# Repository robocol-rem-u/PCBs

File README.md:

# PCBs

PCBs Eagle designs that power REM-U

## Getting Started

1. Install Eagle (students)
2. Open board and schematics

## Built With

* [Eagle](https://www.autodesk.com/products/eagle/overview) - Autodesk EAGLE is powerful, easy-to-use PCB design and schematic software

## Authors

* **Miguel Angel Díaz** - *PCB Design*
* **Oscar Díaz Caballero** - *GitHub Upload* - [alegis277](https://github.com/alegis277)

See also the list of [contributors](https://github.com/robocol-rem-u/PCBs/graphs/contributors) who participated in this project.

## License

This project is licensed under the GNU General Public License v3.0 - see the [LICENSE.txt](LICENSE.txt) file for details

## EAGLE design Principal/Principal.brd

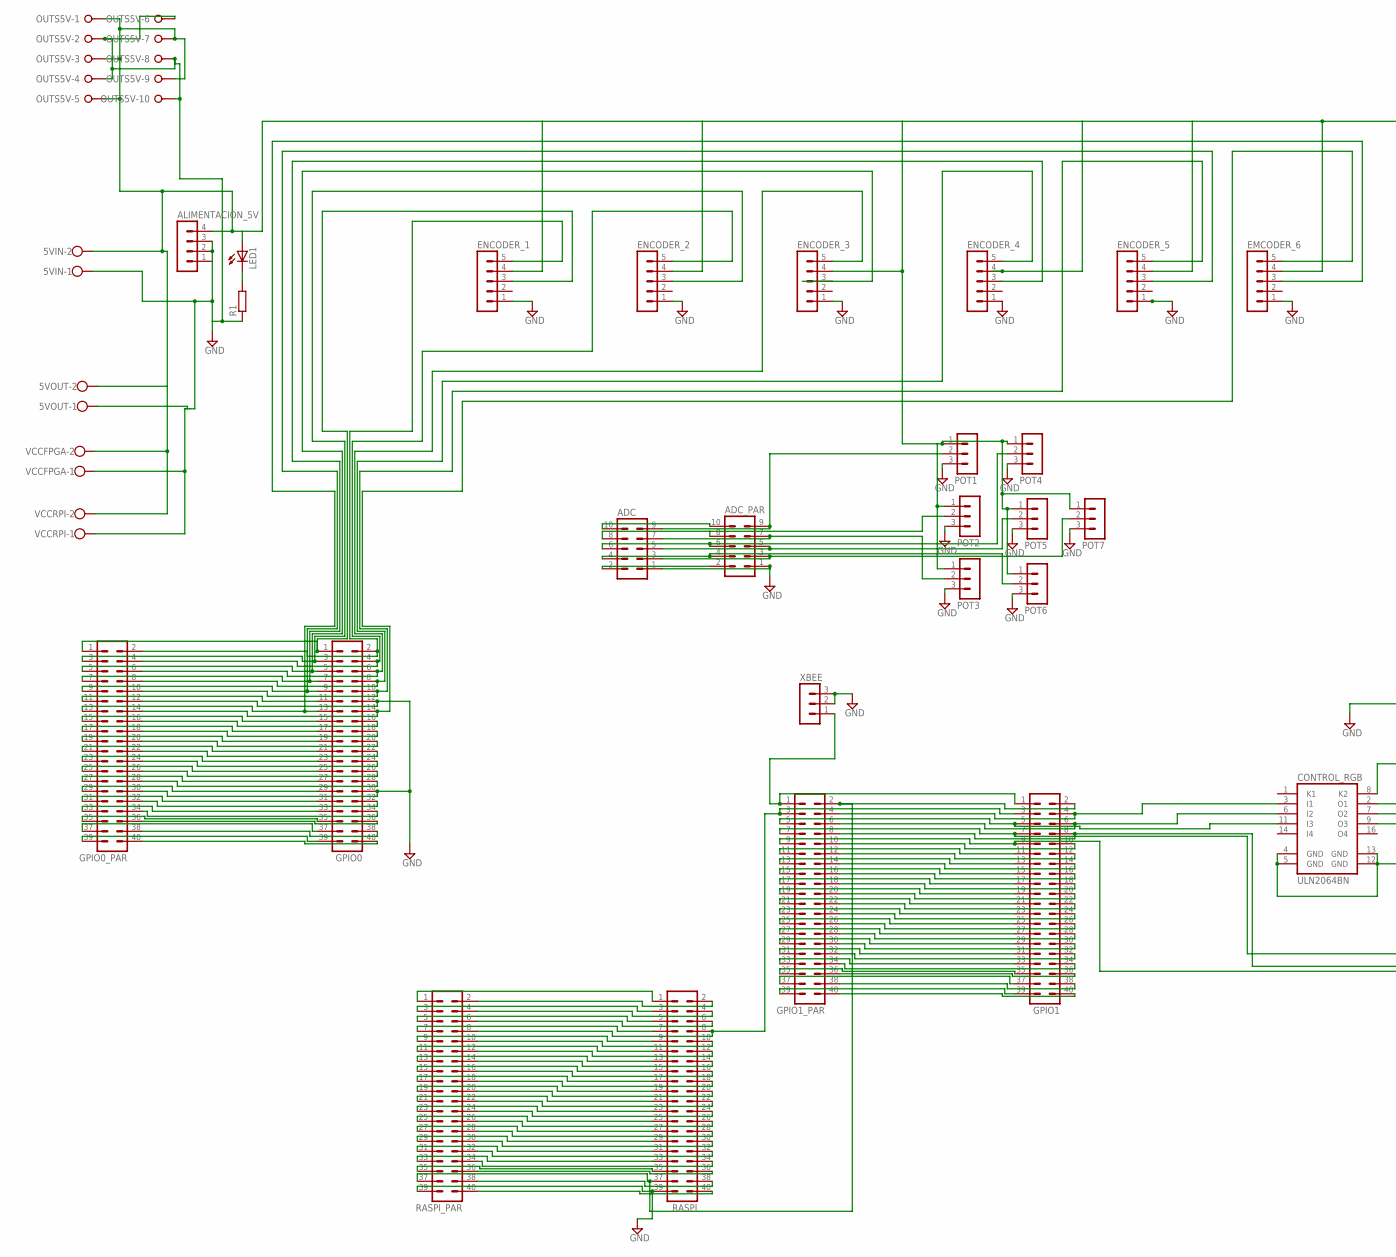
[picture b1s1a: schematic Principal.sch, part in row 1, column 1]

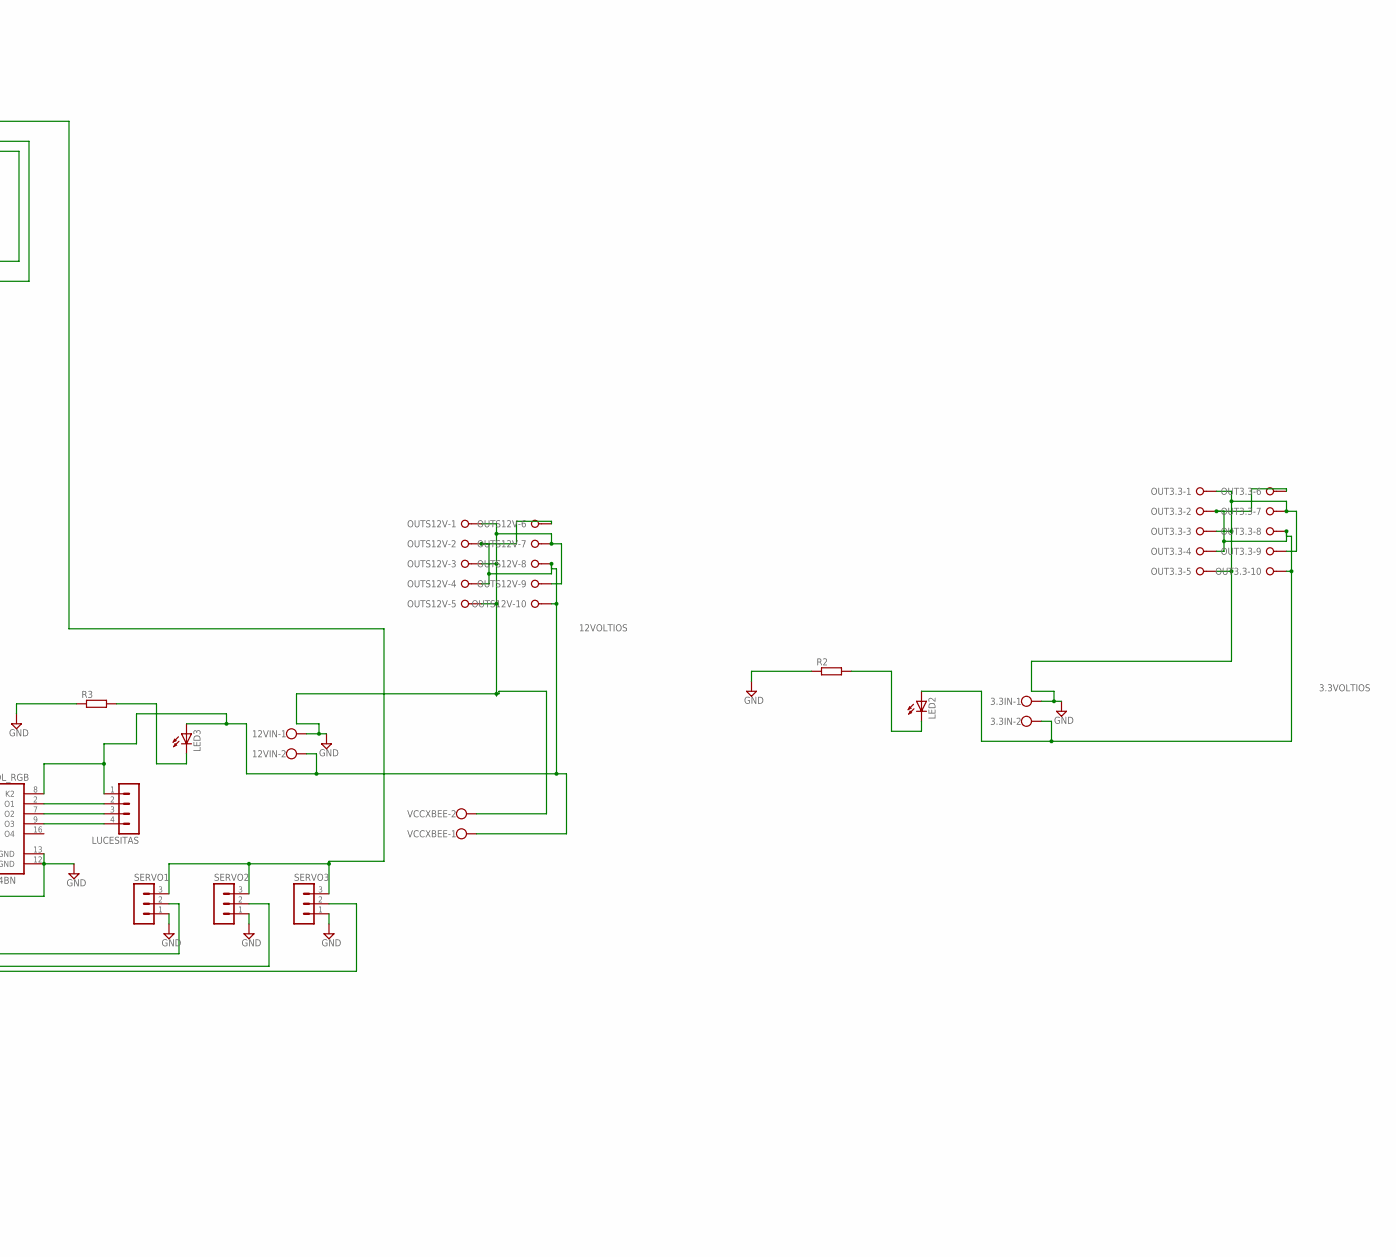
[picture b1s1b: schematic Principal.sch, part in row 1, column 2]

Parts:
3.3IN, 5VIN, 5VOUT, 12VIN: W237-102
ADC: MA05-2
ADC_PAR: MA05-2
ALIMENTACION_5V: MA04-1
CONTROL_RGB: ULN2064BN; DIL16
EMCODER_6: MA05-1
ENCODER_1, ENCODER_2, ENCODER_3, ENCODER_4, ENCODER_5: MA05-1
GPIO0, GPIO0_PAR, GPIO1, GPIO1_PAR: MA20-2
LED1, LED2, LED3: LEDSML0805; SML0805
LUCESITAS: MA04-1
OUT3.3: W237-10P
OUTS5V, OUTS12V: W237-10P
POT1, POT2, POT3, POT4, POT5, POT6, POT7: MA03-1
R1, R2, R3: RR1206; R1206
RASPI: MA20-2
RASPI_PAR: MA20-2
SERVO1, SERVO2, SERVO3: MA03-1
VCCFPGA: W237-102
VCCRPI: W237-102
VCCXBEE: W237-102
XBEE: MA03-1

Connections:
3.3VOLTIOS: 3.3IN.2, LED2.A, OUT3.3.2, OUT3.3.4, OUT3.3.6, OUT3.3.8, OUT3.3.10
12VOLTIOS: 12VIN.2, CONTROL_RGB.8 (K2), LED3.A, LUCESITAS.1, OUTS12V.2, OUTS12V.4, OUTS12V.6, OUTS12V.8, OUTS12V.10, VCCXBEE.1
+5V3: 5VIN.2, 5VOUT.2, ALIMENTACION_5V.4, EMCODER_6.4, ENCODER_1.4, ENCODER_2.4, ENCODER_3.4, ENCODER_4.4, ENCODER_5.4, LED1.A, OUTS5V.1, OUTS5V.3, OUTS5V.5, OUTS5V.7, OUTS5V.9, POT1.1, POT2.1, POT3.1, POT4.1, POT5.1, POT6.1, POT7.1, SERVO1.3, SERVO2.3, SERVO3.3, VCCFPGA.2, VCCRPI.2
GND: 3.3IN.1, 5VIN.1, 5VOUT.1, 12VIN.1, ADC.1, ADC_PAR.1, ALIMENTACION_5V.1, ALIMENTACION_5V.2, ALIMENTACION_5V.3, CONTROL_RGB.4 (GND), CONTROL_RGB.5 (GND), CONTROL_RGB.12 (GND), CONTROL_RGB.13 (GND), EMCODER_6.1, ENCODER_1.1, ENCODER_2.1, ENCODER_3.1, ENCODER_4.1, ENCODER_5.1, GPIO0.12, GPIO0.30, GPIO0_PAR.12, GPIO0_PAR.30, OUT3.3.1, OUT3.3.3, OUT3.3.5, OUT3.3.7, OUT3.3.9, OUTS5V.2, OUTS5V.4, OUTS5V.6, OUTS5V.8, OUTS5V.10, OUTS12V.1, OUTS12V.3, OUTS12V.5, OUTS12V.7, OUTS12V.9, POT1.3, POT2.3, POT3.3, POT4.3, POT5.3, POT6.3, POT7.3, R1.1, R2.1, R3.1, RASPI.39, RASPI_PAR.39, SERVO1.1, SERVO2.1, SERVO3.1, VCCFPGA.1, VCCRPI.1, VCCXBEE.2, XBEE.2, XBEE.3
unnamed: LED2.C, R2.2
unnamed: ENCODER_2.5, GPIO0.4, GPIO0_PAR.4
unnamed: ENCODER_4.5, GPIO0.8, GPIO0_PAR.8
unnamed: ENCODER_5.3, GPIO0.9, GPIO0_PAR.9
unnamed: GPIO0.11, GPIO0_PAR.11
unnamed: EMCODER_6.5, GPIO0.14, GPIO0_PAR.14
unnamed: GPIO0.15, GPIO0_PAR.15
unnamed: GPIO0.16, GPIO0_PAR.16
unnamed: GPIO0.17, GPIO0_PAR.17
unnamed: GPIO0.18, GPIO0_PAR.18
unnamed: GPIO0.19, GPIO0_PAR.19
unnamed: GPIO0.20, GPIO0_PAR.20
unnamed: GPIO0.21, GPIO0_PAR.21
unnamed: GPIO0.22, GPIO0_PAR.22
unnamed: GPIO0.23, GPIO0_PAR.23
unnamed: GPIO0.24, GPIO0_PAR.24
unnamed: GPIO0.25, GPIO0_PAR.25
unnamed: GPIO0.26, GPIO0_PAR.26
unnamed: GPIO0.27, GPIO0_PAR.27
unnamed: GPIO0.28, GPIO0_PAR.28
unnamed: GPIO0.29, GPIO0_PAR.29
unnamed: GPIO0.31, GPIO0_PAR.31
unnamed: GPIO0.32, GPIO0_PAR.32
unnamed: GPIO0.33, GPIO0_PAR.33
unnamed: GPIO0.34, GPIO0_PAR.34
unnamed: GPIO0.35, GPIO0_PAR.35
unnamed: GPIO0.36, GPIO0_PAR.36
unnamed: GPIO0.37, GPIO0_PAR.37
unnamed: GPIO0.38, GPIO0_PAR.38
unnamed: GPIO0.39, GPIO0_PAR.39
unnamed: GPIO0.40, GPIO0_PAR.40
unnamed: GPIO1.1, GPIO1_PAR.1, XBEE.1
unnamed: GPIO1.2, GPIO1_PAR.2, RASPI.37, RASPI_PAR.37
unnamed: CONTROL_RGB.3 (I1), GPIO1.4, GPIO1_PAR.4
unnamed: CONTROL_RGB.11 (I3), GPIO1.5, GPIO1_PAR.5
unnamed: CONTROL_RGB.6 (I2), GPIO1.6, GPIO1_PAR.6
unnamed: GPIO1.7, GPIO1_PAR.7, SERVO1.2
unnamed: GPIO1.8, GPIO1_PAR.8, SERVO2.2
unnamed: GPIO1.9, GPIO1_PAR.9, SERVO3.2
unnamed: GPIO1.10, GPIO1_PAR.10
unnamed: GPIO1.11, GPIO1_PAR.11
unnamed: GPIO1.12, GPIO1_PAR.12
unnamed: GPIO1.13, GPIO1_PAR.13
unnamed: GPIO1.14, GPIO1_PAR.14
unnamed: GPIO1.15, GPIO1_PAR.15
unnamed: GPIO1.16, GPIO1_PAR.16
unnamed: GPIO1.17, GPIO1_PAR.17
unnamed: GPIO1.18, GPIO1_PAR.18
unnamed: GPIO1.19, GPIO1_PAR.19
unnamed: GPIO1.20, GPIO1_PAR.20
unnamed: GPIO1.21, GPIO1_PAR.21
unnamed: GPIO1.22, GPIO1_PAR.22
unnamed: GPIO1.23, GPIO1_PAR.23
unnamed: GPIO1.24, GPIO1_PAR.24
unnamed: GPIO1.25, GPIO1_PAR.25
unnamed: GPIO1.26, GPIO1_PAR.26
unnamed: GPIO1.27, GPIO1_PAR.27
unnamed: GPIO1.28, GPIO1_PAR.28
unnamed: GPIO1.29, GPIO1_PAR.29
unnamed: GPIO1.30, GPIO1_PAR.30
unnamed: GPIO1.31, GPIO1_PAR.31
unnamed: GPIO1.32, GPIO1_PAR.32
unnamed: GPIO1.33, GPIO1_PAR.33
unnamed: GPIO1.34, GPIO1_PAR.34
unnamed: GPIO1.35, GPIO1_PAR.35
unnamed: GPIO1.36, GPIO1_PAR.36
unnamed: GPIO1.37, GPIO1_PAR.37
unnamed: GPIO1.38, GPIO1_PAR.38
unnamed: GPIO1.39, GPIO1_PAR.39
unnamed: GPIO1.40, GPIO1_PAR.40
unnamed: RASPI.1, RASPI_PAR.1
unnamed: RASPI.2, RASPI_PAR.2
unnamed: RASPI.3, RASPI_PAR.3
unnamed: RASPI.4, RASPI_PAR.4
unnamed: RASPI.5, RASPI_PAR.5
unnamed: RASPI.6, RASPI_PAR.6
unnamed: RASPI.7, RASPI_PAR.7
unnamed: GPIO1.3, GPIO1_PAR.3, RASPI.8, RASPI_PAR.8
unnamed: RASPI.9, RASPI_PAR.9
unnamed: RASPI.10, RASPI_PAR.10
unnamed: RASPI.11, RASPI_PAR.11
unnamed: RASPI.12, RASPI_PAR.12
unnamed: RASPI.13, RASPI_PAR.13
unnamed: RASPI.14, RASPI_PAR.14
unnamed: RASPI.15, RASPI_PAR.15
unnamed: RASPI.16, RASPI_PAR.16
unnamed: RASPI.17, RASPI_PAR.17
unnamed: RASPI.18, RASPI_PAR.18
unnamed: RASPI.19, RASPI_PAR.19
unnamed: RASPI.20, RASPI_PAR.20
unnamed: RASPI.21, RASPI_PAR.21
unnamed: RASPI.22, RASPI_PAR.22
unnamed: RASPI.23, RASPI_PAR.23
unnamed: RASPI.24, RASPI_PAR.24
unnamed: RASPI.25, RASPI_PAR.25
unnamed: RASPI.26, RASPI_PAR.26
unnamed: RASPI.27, RASPI_PAR.27
unnamed: RASPI.28, RASPI_PAR.28
unnamed: RASPI.29, RASPI_PAR.29
unnamed: RASPI.30, RASPI_PAR.30
unnamed: RASPI.31, RASPI_PAR.31
unnamed: RASPI.32, RASPI_PAR.32
unnamed: RASPI.33, RASPI_PAR.33
unnamed: RASPI.34, RASPI_PAR.34
unnamed: RASPI.35, RASPI_PAR.35
unnamed: RASPI.36, RASPI_PAR.36
unnamed: RASPI.38, RASPI_PAR.38
unnamed: RASPI.40, RASPI_PAR.40
unnamed: ADC.10, ADC_PAR.10
unnamed: ADC.9, ADC_PAR.9, POT1.2
unnamed: ADC.8, ADC_PAR.8, POT2.2
unnamed: ADC.7, ADC_PAR.7, POT3.2
unnamed: ADC.6, ADC_PAR.6, POT4.2
unnamed: ADC.5, ADC_PAR.5, POT5.2
unnamed: ADC.4, ADC_PAR.4, POT6.2
unnamed: ADC.3, ADC_PAR.3, POT7.2
unnamed: ADC.2, ADC_PAR.2
unnamed: ENCODER_1.3, GPIO0.1, GPIO0_PAR.1
unnamed: ENCODER_1.5, GPIO0.2, GPIO0_PAR.2
unnamed: ENCODER_2.3, GPIO0.3, GPIO0_PAR.3
unnamed: ENCODER_3.3, GPIO0.5, GPIO0_PAR.5
unnamed: ENCODER_3.5, GPIO0.6, GPIO0_PAR.6
unnamed: ENCODER_4.3, GPIO0.7, GPIO0_PAR.7
unnamed: ENCODER_5.5, GPIO0.10, GPIO0_PAR.10
unnamed: EMCODER_6.3, GPIO0.13, GPIO0_PAR.13
unnamed: LED1.C, R1.2
unnamed: LED3.C, R3.2
unnamed: CONTROL_RGB.2 (O1), LUCESITAS.2
unnamed: CONTROL_RGB.7 (O2), LUCESITAS.3
unnamed: CONTROL_RGB.9 (O3), LUCESITAS.4

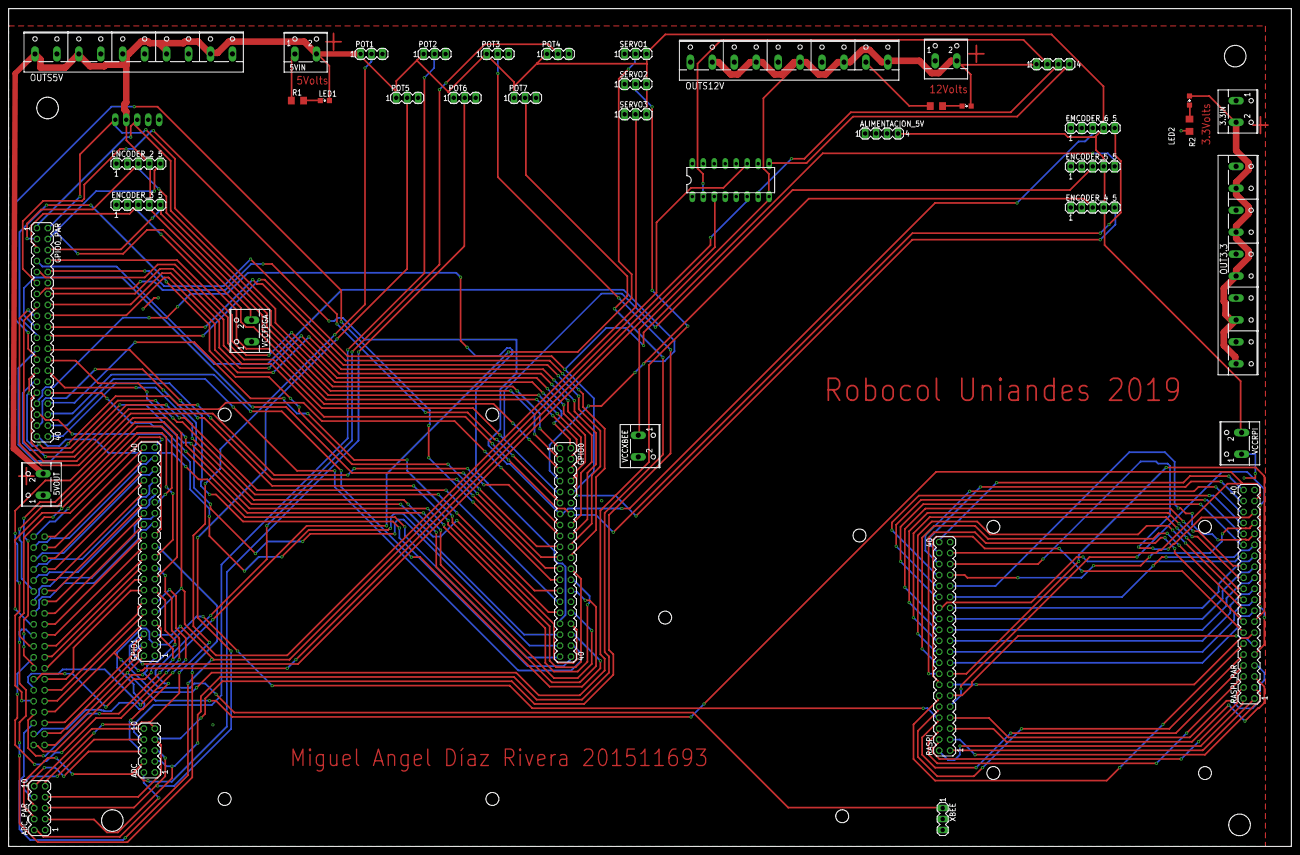
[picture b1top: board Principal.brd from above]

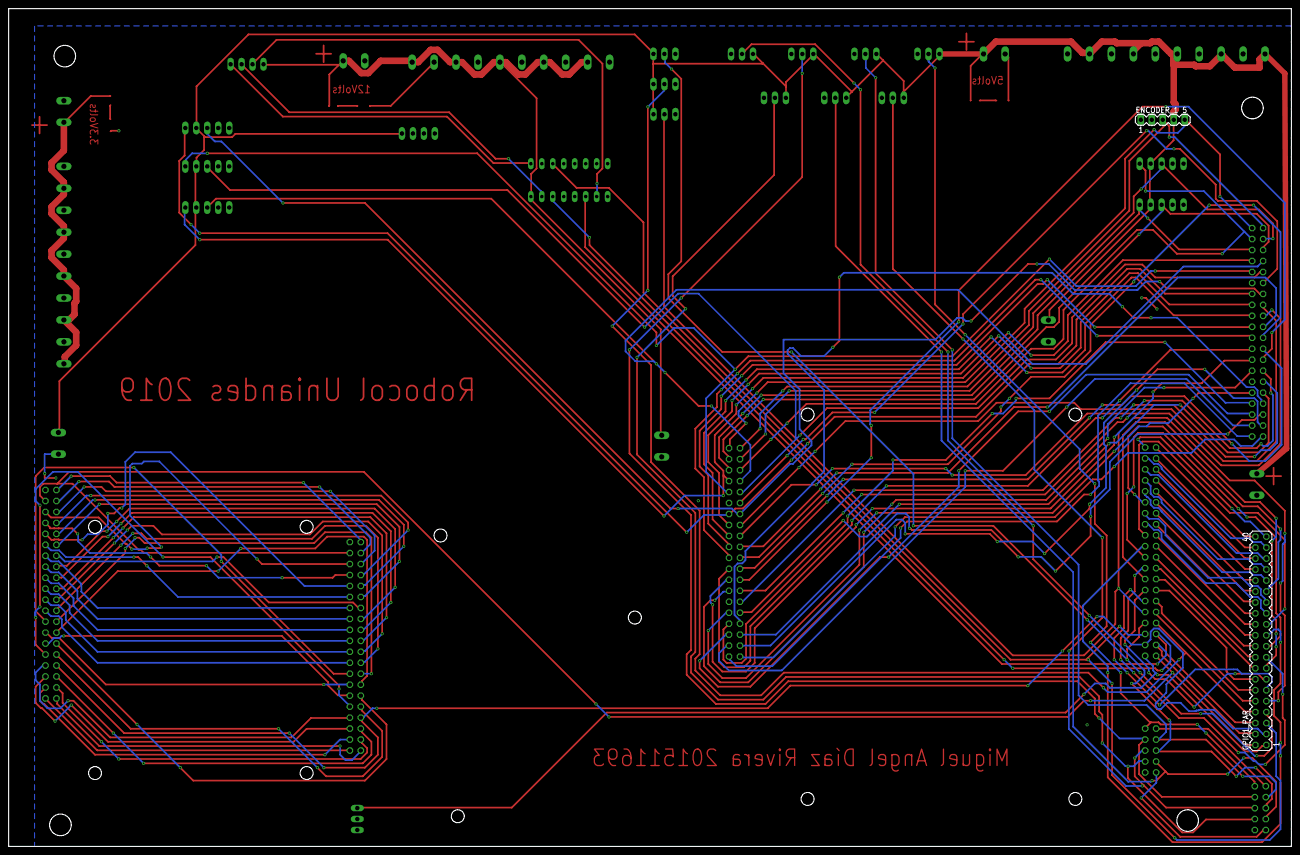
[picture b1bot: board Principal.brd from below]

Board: 2 copper layers, 297.0 x 194.0 mm, 44 parts (2 on the bottom side), 134 nets.

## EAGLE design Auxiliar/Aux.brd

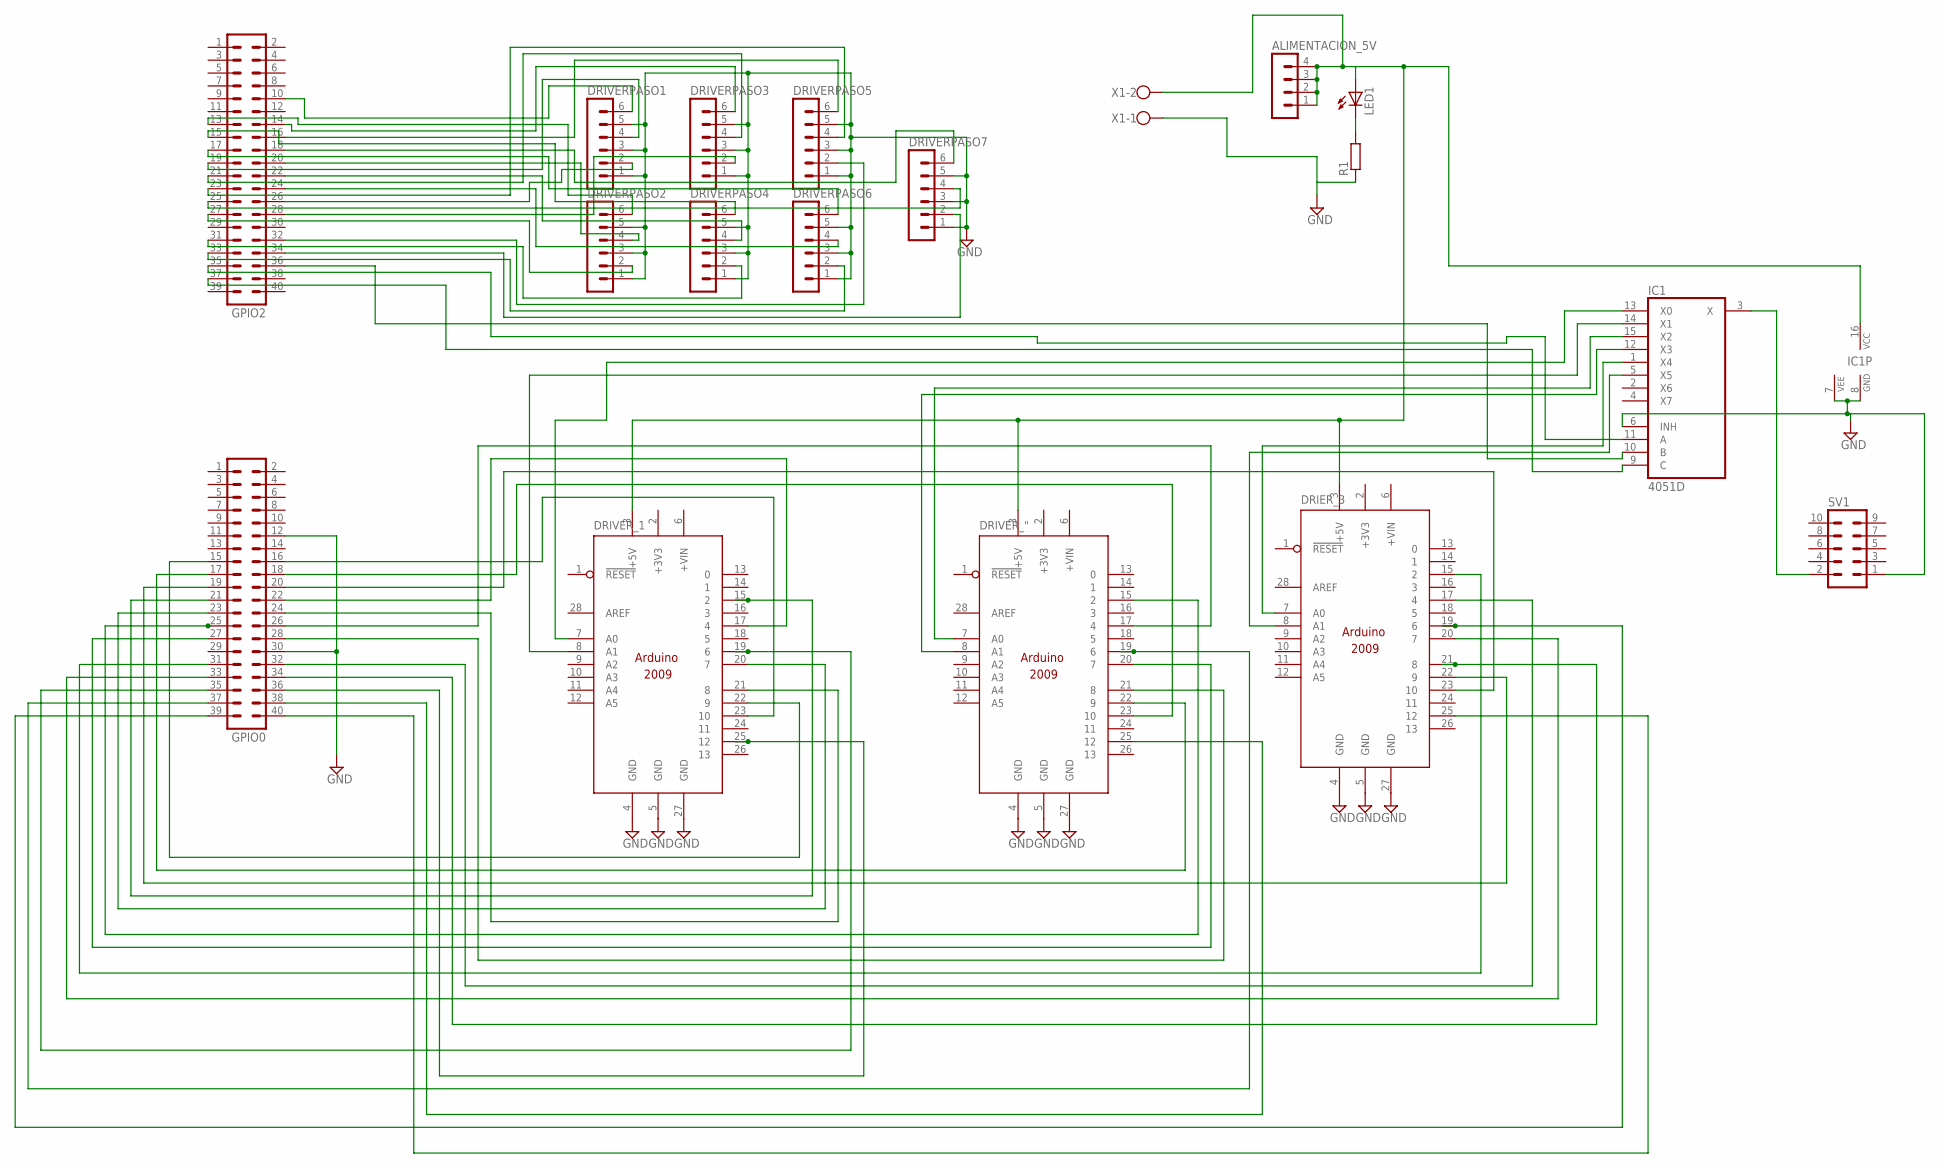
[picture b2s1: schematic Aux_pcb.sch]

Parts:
ALIMENTACION_5V: MA04-1
DRIER_3: ARDUINO2009_10; ARDUINO2009
DRIVERPASO1, DRIVERPASO2, DRIVERPASO3, DRIVERPASO4, DRIVERPASO5, DRIVERPASO6, DRIVERPASO7: MA06-1
DRIVER_1: ARDUINO2009_10; ARDUINO2009
DRIVER_": ARDUINO2009_10; ARDUINO2009
GPIO0, GPIO2: MA20-2
IC1: 4051D; SO16
LED1: LEDSML0805; SML0805
R1: RR1206; R1206
SV1: MA05-2
X1: W237-102

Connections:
+3V3: DRIER_3.2 (+3V3), DRIVER_1.2 (+3V3), DRIVER_".2 (+3V3)
+5V: ALIMENTACION_5V.1, ALIMENTACION_5V.2, ALIMENTACION_5V.3, ALIMENTACION_5V.4, DRIER_3.3 (+5V), DRIVER_1.3 (+5V), DRIVER_".3 (+5V), IC1.16 (VCC), LED1.A, X1.2
GND: DRIER_3.4 (GND), DRIER_3.5 (GND), DRIER_3.27 (GND), DRIVERPASO1.1, DRIVERPASO1.3, DRIVERPASO1.5, DRIVERPASO2.1, DRIVERPASO2.3, DRIVERPASO2.5, DRIVERPASO3.1, DRIVERPASO3.3, DRIVERPASO3.5, DRIVERPASO4.1, DRIVERPASO4.3, DRIVERPASO4.5, DRIVERPASO5.1, DRIVERPASO5.3, DRIVERPASO5.5, DRIVERPASO6.1, DRIVERPASO6.3, DRIVERPASO6.5, DRIVERPASO7.1, DRIVERPASO7.3, DRIVERPASO7.5, DRIVER_1.4 (GND), DRIVER_1.5 (GND), DRIVER_1.27 (GND), DRIVER_".4 (GND), DRIVER_".5 (GND), DRIVER_".27 (GND), GPIO0.12, GPIO0.30, IC1.6 (INH), IC1.7 (VEE), IC1.8 (GND), R1.1, SV1.1, X1.1
unnamed: DRIVER_1.7 (A0), IC1.13 (X0)
unnamed: DRIVERPASO1.6, GPIO2.10
unnamed: DRIVERPASO2.6, GPIO2.13
unnamed: DRIVERPASO3.6, GPIO2.14
unnamed: DRIVERPASO4.6, GPIO2.15
unnamed: DRIVERPASO5.6, GPIO2.16
unnamed: DRIVERPASO6.6, GPIO2.17
unnamed: DRIVERPASO7.6, GPIO2.18
unnamed: DRIVER_1.22 (9), GPIO0.15
unnamed: DRIVER_1.23 (10), GPIO0.16
unnamed: DRIVER_".22 (9), GPIO0.17
unnamed: DRIVER_".23 (10), GPIO0.18
unnamed: DRIER_3.22 (9), GPIO0.19
unnamed: DRIER_3.23 (10), GPIO0.20
unnamed: DRIVER_1.15 (2), GPIO0.21
unnamed: DRIVER_1.17 (4), GPIO0.22
unnamed: DRIVER_1.20 (7), GPIO0.23
unnamed: DRIVER_1.21 (8), GPIO0.24
unnamed: DRIVER_".15 (2), GPIO0.25
unnamed: DRIVER_".17 (4), GPIO0.26
unnamed: DRIVER_".20 (7), GPIO0.27
unnamed: DRIVER_".21 (8), GPIO0.28
unnamed: DRIER_3.15 (2), GPIO0.31
unnamed: DRIER_3.17 (4), GPIO0.32
unnamed: DRIER_3.20 (7), GPIO0.33
unnamed: DRIER_3.21 (8), GPIO0.34
unnamed: DRIVER_1.19 (6), GPIO0.35
unnamed: DRIVER_1.25 (12), GPIO0.36
unnamed: DRIVER_".19 (6), GPIO0.37
unnamed: DRIVER_".25 (12), GPIO0.38
unnamed: DRIER_3.19 (6), GPIO0.39
unnamed: DRIER_3.25 (12), GPIO0.40
unnamed: DRIVERPASO1.4, GPIO2.19
unnamed: DRIVERPASO2.4, GPIO2.20
unnamed: DRIVERPASO3.4, GPIO2.21
unnamed: DRIVERPASO4.4, GPIO2.22
unnamed: DRIVERPASO5.4, GPIO2.23
unnamed: DRIVERPASO6.4, GPIO2.24
unnamed: DRIVERPASO7.4, GPIO2.25
unnamed: DRIVERPASO1.2, GPIO2.26
unnamed: DRIVERPASO2.2, GPIO2.27
unnamed: DRIVERPASO3.2, GPIO2.28
unnamed: DRIVERPASO4.2, GPIO2.31
unnamed: DRIVERPASO5.2, GPIO2.32
unnamed: DRIVERPASO6.2, GPIO2.33
unnamed: DRIVERPASO7.2, GPIO2.34
unnamed: DRIVER_1.8 (A1), IC1.14 (X1)
unnamed: DRIVER_".7 (A0), IC1.15 (X2)
unnamed: DRIVER_".8 (A1), IC1.12 (X3)
unnamed: DRIER_3.7 (A0), IC1.1 (X4)
unnamed: DRIER_3.8 (A1), IC1.5 (X5)
unnamed: IC1.3 (X), SV1.2
unnamed: GPIO2.35, IC1.11 (A)
unnamed: GPIO2.36, IC1.10 (B)
unnamed: GPIO2.37, IC1.9 (C)
unnamed: LED1.C, R1.2

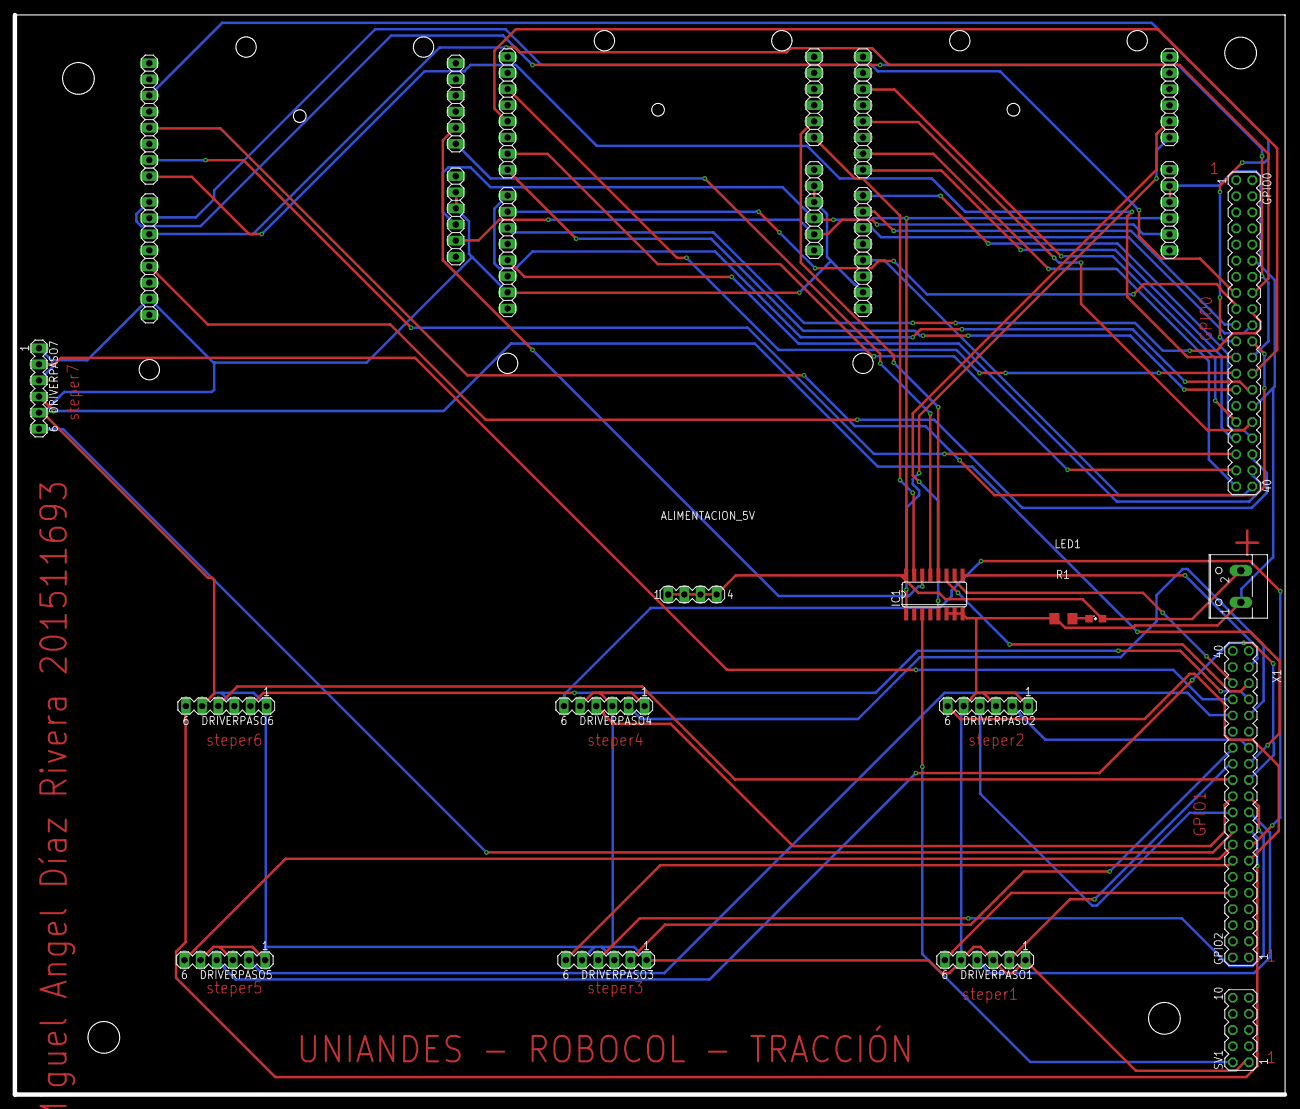
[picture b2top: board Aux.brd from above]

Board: 2 copper layers, 200.0 x 170.0 mm, 18 parts (0 on the bottom side), 59 nets.

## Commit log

2019-04-12 README update
2019-04-13 Name corrections
